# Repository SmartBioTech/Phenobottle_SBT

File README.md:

# CzechGlobe SmartBioTech Phenobottle

This project is originaly based on the Phenobottle from Harvey Bates. URL: https://github.com/HarveyBates/Phenobottle

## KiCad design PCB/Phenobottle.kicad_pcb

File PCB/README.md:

# PCB

Designed in KiCAD 5.99 (nightly)

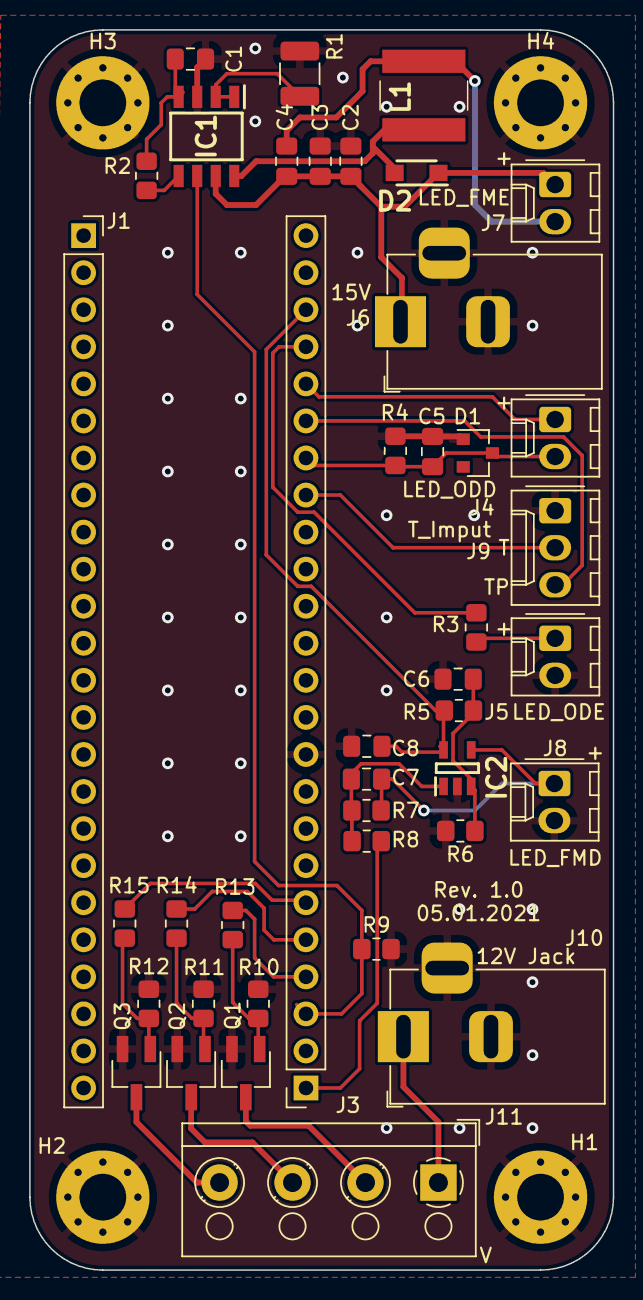
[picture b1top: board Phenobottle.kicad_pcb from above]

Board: 2 copper layers, 40.0 x 85.0 mm, 45 parts (0 on the bottom side), 29 nets.

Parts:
C1: 1uF; C_0805_2012Metric_Pad1.18x1.45mm_HandSolder
C2: 4.7uF; C_0805_2012Metric_Pad1.18x1.45mm_HandSolder
C3: 100nF; C_0805_2012Metric_Pad1.18x1.45mm_HandSolder
C4: DNP; C_0805_2012Metric_Pad1.18x1.45mm_HandSolder
C5: 100nf; C_0805_2012Metric_Pad1.18x1.45mm_HandSolder
C6, C8: 100n; C_0805_2012Metric_Pad1.18x1.45mm_HandSolder
C7: Cf; C_0805_2012Metric_Pad1.18x1.45mm_HandSolder
D1: BZX84C3V6LT1G; D_SOT-23_ANK
D2: MBR140SFT3G; SODFL3616X98N
H1, H2, H3, H4: MountingHole_Pad; MountingHole_3.2mm_M3_Pad_Via
IC1: NCL30160DR2G; SOIC127P600X175-8N
IC2: OPA320AIDBVR; SOT95P280X145-5N
J1, J3: Conn_01x24_Female; PinSocket_1x24_P2.54mm_Vertical
J4: LED_ODD; Molex_KK-254_AE-6410-02A_1x02_P2.54mm_Vertical
J5: LED_ODE; Molex_KK-254_AE-6410-02A_1x02_P2.54mm_Vertical
J6: 15V; BarrelJack_Horizontal
J7: LED_FME; Molex_KK-254_AE-6410-02A_1x02_P2.54mm_Vertical
J8: LED_FMD; Molex_KK-254_AE-6410-02A_1x02_P2.54mm_Vertical
J9: T_Imput; Molex_KK-254_AE-6410-03A_1x03_P2.54mm_Vertical
J10: 12V Jack; BarrelJack_Horizontal
J11: RGB; TerminalBlock_RND_205-00003_1x04_P5.00mm_Horizontal
L1: 15uH@0.19R; NR6045T150M
Q1, Q2, Q3: DMN1019USN; SC-59_Handsoldering
R1: 0.287; R_1210_3225Metric_Pad1.30x2.65mm_HandSolder
R2: 24K; R_0805_2012Metric_Pad1.20x1.40mm_HandSolder
R3, R6: 220; R_0805_2012Metric_Pad1.20x1.40mm_HandSolder
R4: R; R_0805_2012Metric_Pad1.20x1.40mm_HandSolder
R5: 20K; R_0805_2012Metric_Pad1.20x1.40mm_HandSolder
R7: 4.7M; R_0805_2012Metric_Pad1.20x1.40mm_HandSolder
R8: 47; R_0805_2012Metric_Pad1.20x1.40mm_HandSolder
R9: 4k7; R_0805_2012Metric_Pad1.20x1.40mm_HandSolder
R10: 10K; R_0805_2012Metric_Pad1.20x1.40mm_HandSolder
R11, R12: 10k; R_0805_2012Metric_Pad1.20x1.40mm_HandSolder
R13, R14, R15: 165R; R_0805_2012Metric_Pad1.20x1.40mm_HandSolder

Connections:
/1a1: C2.1, C3.1, C4.2, D2.1, IC1.7 (VIN), J6.1, J7.1
/1a2: D2.2, IC1.8 (LX), L1.1
/1a3: C4.1, J7.2, L1.2
/LED1: J11.2, Q1.3 (D)
/LED2: J11.3, Q2.3 (D)
/LED3: J11.4, Q3.3 (D)
/LEDV: J10.1, J11.1
Brightness: IC1.6 (~DIM~/ENABLE), J3.3, R9.1
Fluro: J3.1, R8.2
GND: C1.2, C2.2, C3.2, C5.1, C6.2, C8.2, D1.2 (A), H1.1, H2.1, H3.1, H4.1, IC1.3 (GND), IC2.2 (V-), J3.10, J5.2, J6.2, J6.3, J8.2, J9.1, J10.2, J10.3, Q1.2 (S), Q2.2 (S), Q3.2 (S), R1.2, R4.2, R6.1, R9.2, R10.2, R11.2, R12.2
LED_B: J3.4, R13.1
LED_G: J3.5, R14.1
LED_R: J3.6, R15.1
unnamed: C1.1, IC1.4 (VCC), R2.1
unnamed: C6.1, IC2.3 (+IN), R5.1, R6.2
unnamed: C7.1, IC2.4 (-IN), J8.1, R7.1
unnamed: C7.2, IC2.1 (OUT), R7.2, R8.1
unnamed: IC1.1 (CS_1), IC1.2 (CS_2), R1.1
unnamed: IC1.5 (ROT), R2.2
unnamed: J5.1, R3.2
unnamed: Q1.1 (G), R10.1, R13.2
unnamed: Q2.1 (G), R11.1, R14.2
unnamed: Q3.1 (G), R12.1, R15.2
ODdPower: J3.20, J4.1
ODdetect: C5.2, D1.1 (K), J3.18, J4.2, R4.1
ODePower: J3.21, R3.1
TempPower: J3.19, J9.3
Temperature: J3.17, J9.2
VCC: C8.1, IC2.5 (V+), J3.22, R5.2

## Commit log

2022-07-25 Initial project files upload
